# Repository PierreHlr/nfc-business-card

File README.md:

# NFC business card

A business card that is also a printed circuit board: tap it with a phone and
it opens my portfolio. No battery, no app, no microcontroller. The antenna is
etched directly into the PCB and was designed from first principles.

<table>
  <tr>
    <td align="center"><br><sub>Front: name, title and contact</sub></td>
    <td align="center"><br><sub>Back: NFC chip, QR code fallback, antenna under the mask</sub></td>
  </tr>
</table>

## At a glance

| | |
|---|---|
| Format | ISO/IEC 7810 ID-1 (85.6 × 53.98 mm), FR-4 0.8 mm, black mask, ENIG |
| NFC chip | NXP NTAG213F, NFC Forum Type 2 Tag, ISO/IEC 14443 A, 144 B of memory |
| Antenna | 4-turn printed spiral, 80 × 48 mm, 1.0 mm traces, 0.5 mm gaps |
| Inductance | **2.24 µH**, from two independent models agreeing within 2.5 % |
| Resonance | **14.7 MHz** untuned, tunable down to 13.56 MHz with about 9 pF |
| Harvested EMF | 2.0 V rms at the minimum ISO field of 1.5 A/m |
| Payload | NDEF URI record, 28 bytes: `https://pierrehlr.github.io/` |
| Fallback | 25 × 25 QR code (alphanumeric mode), 0.7 mm modules, silkscreen knockout |
| Tools | KiCad 10, Python (standard library), JLCPCB PCB + assembly |

## How it works

At 13.56 MHz the wavelength is 22 m, so a phone a few centimetres away is deep
in the **near field**. The phone's coil and the card's spiral act as a loosely
coupled transformer.

* The phone's field **powers** the chip through Faraday induction.
* The chip **answers** by modulating its own load, a change the phone senses
  through the mutual inductance.

The card antenna and the chip's 50 pF input capacitance form a **parallel LC
resonator**. Its resonance frequency must sit close to the carrier:

$$
f_0 = \frac{1}{2\pi\sqrt{L (C_i + C_{\mathrm{par}} + C_{\mathrm{tune}})}}
$$

Without a network analyser to measure it, the design relies on calculation,
so the inductance was computed in two unrelated ways:

* a **segment-by-segment partial-inductance sum** (Greenhouse method, exact
  Neumann integrals), validated against a closed-form square loop to 0.05 %;
* the **empirical printed-coil formula** of ST AN2972.

They agree within 2.5 %. The antenna was deliberately tuned a little above
13.56 MHz, because capacitance can only be added. Two empty 0603 footprints
allow the final tuning to be found by measuring read distance.

➡️ **Full derivations, with every number and figure:
[docs/physics.md](docs/physics.md)**

## Repository layout

```
.
├── README.md
├── calc/                      # physics models and figure generation (Python, no dependencies)
│   ├── antenna.py             #   Greenhouse inductance, empirical formula, parasitics, losses
│   ├── report.py              #   prints every number used in the docs
│   └── figures.py             #   regenerates docs/images/*.svg
├── docs/
│   ├── physics.md             # design calculations (start here)
│   ├── hardware.md            # chip choice, schematic, footprints, layout, manufacturing
│   ├── 00_cahier_des_charges.md   # original specification and decision log (French)
│   └── images/
├── Carte_NFC_KiCad/           # KiCad 10 project
│   ├── Carte_NFC_KiCad.kicad_{pro,sch,pcb}
│   ├── carte_nfc.pretty/      #   custom footprints: HXSON4, 4-turn net-tie antenna
│   └── production/            #   Gerbers, drill files, BOM and placement for JLCPCB
└── carte_nfc.kicad_sym        # custom symbol (NTAG213F)
```

## Reproduce

```bash
# physics numbers and figures (any Python 3)
python calc/report.py
python calc/figures.py
```

Open `Carte_NFC_KiCad/Carte_NFC_KiCad.kicad_pro` with KiCad 10. The schematic
embeds its symbols. To edit the NTAG213F symbol, add
`carte_nfc.kicad_sym` to your symbol library table under the nickname
`carte_nfc`. The footprint library is already declared at project level.

## Status

- [x] Requirements, chip selection, schematic
- [x] Antenna design (two models) and custom footprints
- [x] PCB layout, artwork, DRC
- [x] Fabrication files, order placed with JLCPCB (5 assembled cards)
- [ ] Read-distance measurements and capacitor tuning sweep
- [ ] NDEF programming and write-lock
- [ ] Photos of the real cards

Hardware details and KiCad lessons learned are in
[docs/hardware.md](docs/hardware.md).

---

**Pierre HILAIREAU**, embedded systems student · [pierrehlr.github.io](https://pierrehlr.github.io/)

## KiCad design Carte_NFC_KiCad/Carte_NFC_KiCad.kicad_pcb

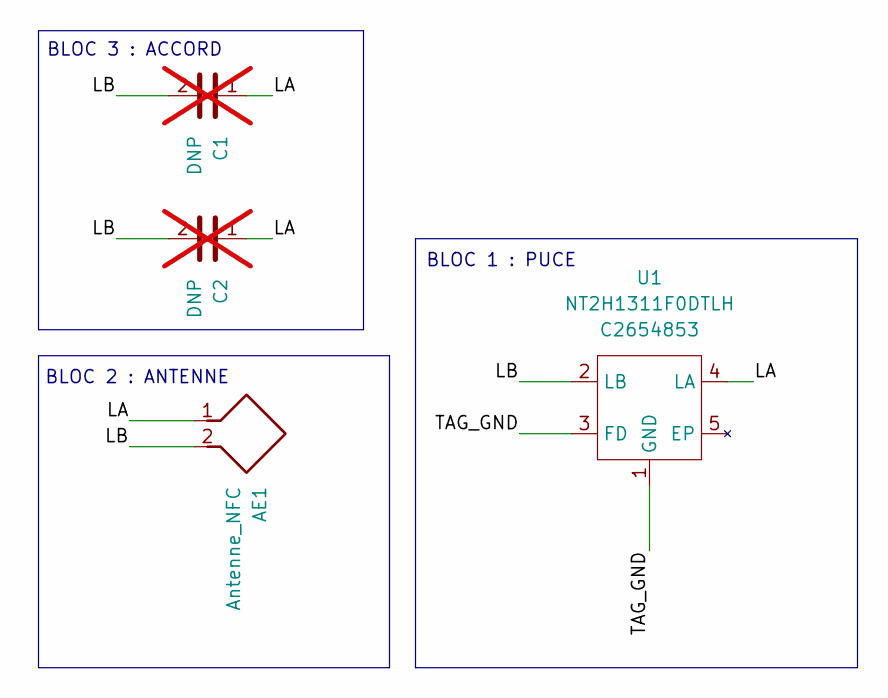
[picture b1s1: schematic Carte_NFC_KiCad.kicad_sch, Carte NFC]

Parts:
AE1: Antenne_NFC; Antenne_NFC_80x48mm_4T
C1, C2: DNP; C_0603_1608Metric; not fitted
U1: NT2H1311F0DTLH; NXP_HXSON-4-1EP_1.5x2mm_P0.5mm; LCSC C2654853

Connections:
/LA: AE1.1, C1.1, C2.1, U1.4 (LA)
/LB: AE1.2, C1.2, C2.2, U1.2 (LB)
/TAG_GND: U1.1 (GND), U1.3 (FD)

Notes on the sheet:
BLOC 2 : ANTENNE
BLOC 3 : ACCORD
BLOC 1 : PUCE

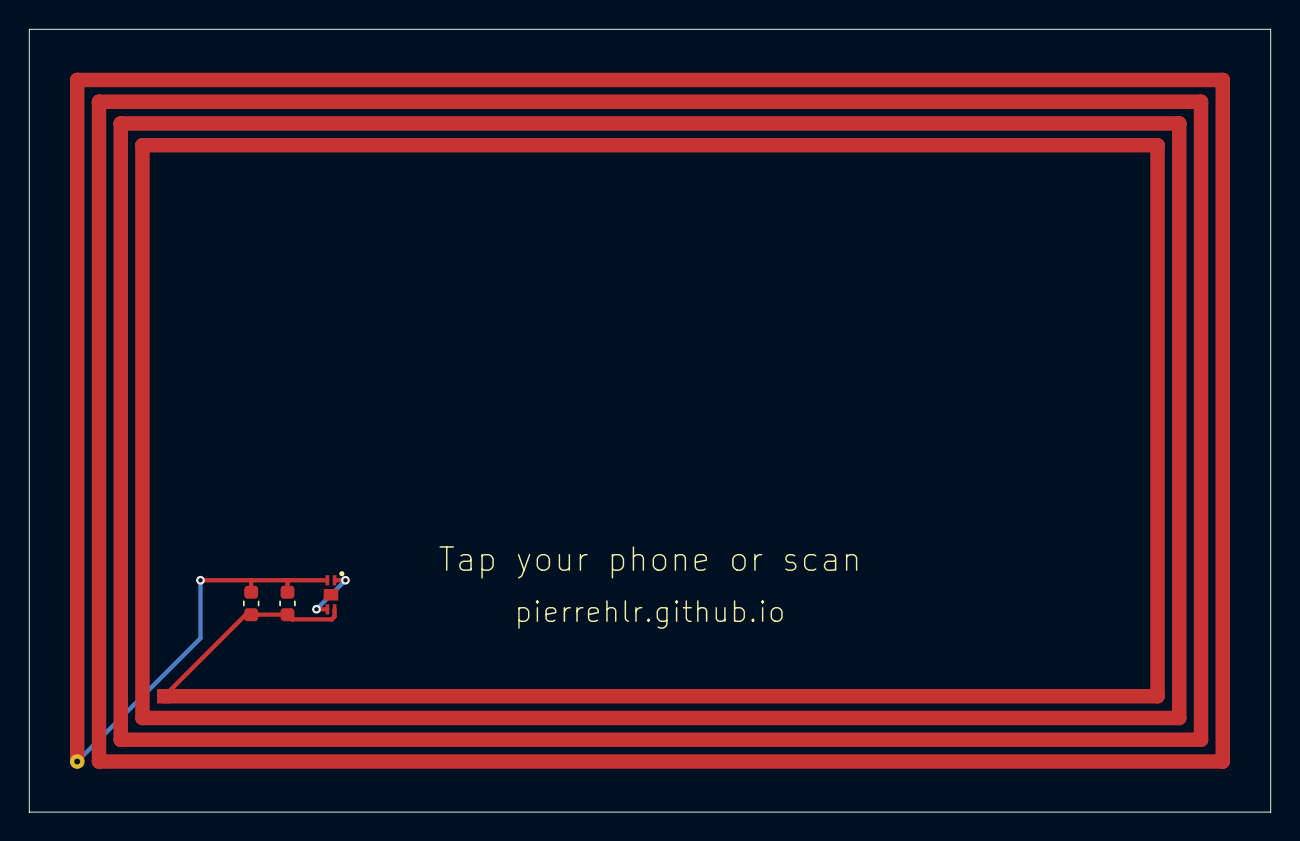
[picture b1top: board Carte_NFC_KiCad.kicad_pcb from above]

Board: 2 copper layers, 85.6 x 54.0 mm, 4 parts (0 on the bottom side), 3 nets.

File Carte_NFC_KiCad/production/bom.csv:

Designator,Footprint,Quantity,Value,LCSC Part #
"C1, C2",0603,2,DNP,
U1,NXP_HXSON-4-1EP_1.5x2mm_P0.5mm,1,NT2H1311F0DTLH,C2654853
